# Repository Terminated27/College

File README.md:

# College
This is everything I have done in college so far.

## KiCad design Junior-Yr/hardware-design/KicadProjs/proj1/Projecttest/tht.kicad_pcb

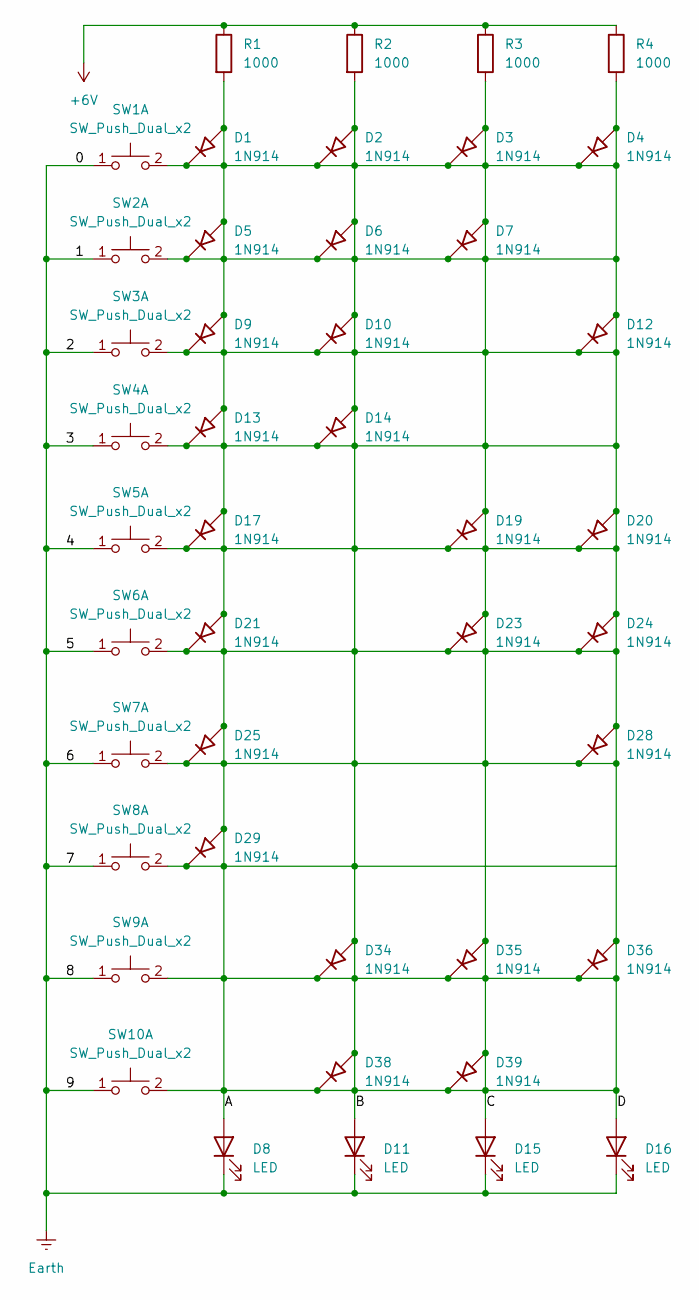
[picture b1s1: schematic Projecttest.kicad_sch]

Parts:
D1, D2, D3, D4, D5, D6, D7, D9, D10, D12, D13, D14, D17, D19, D20, D21, D23, D24, D25, D28, D29, D34, D35, D36, D38, D39: 1N914; AFL-W2C8.9D
D8, D11, D15, D16: LED; LED_D1.8mm_W1.8mm_H2.4mm_Horizontal_O1.27mm_Z1.6mm
R1, R2, R3, R4: 1000; R_Axial_DIN0204_L3.6mm_D1.6mm_P2.54mm_Vertical
SW1, SW2, SW3, SW4, SW5, SW6, SW7, SW8, SW9, SW10: SW_Push_Dual_x2; SW_Cherry_MX_1.00u_PCB

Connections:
+6V: R1.1, R2.1, R3.1, R4.1
/A: D1.1 (K), D1.2 (A), D2.1 (K), D2.2 (A), D3.1 (K), D3.2 (A), D4.1 (K), D4.2 (A), D5.1 (K), D5.2 (A), D6.1 (K), D6.2 (A), D7.1 (K), D7.2 (A), D8.2 (A), D9.1 (K), D9.2 (A), D10.1 (K), D10.2 (A), D11.2 (A), D12.1 (K), D12.2 (A), D13.1 (K), D13.2 (A), D14.1 (K), D14.2 (A), D15.2 (A), D16.2 (A), D17.1 (K), D17.2 (A), D19.1 (K), D19.2 (A), D20.1 (K), D20.2 (A), D21.1 (K), D21.2 (A), D23.1 (K), D23.2 (A), D24.1 (K), D24.2 (A), D25.1 (K), D25.2 (A), D28.1 (K), D28.2 (A), D29.1 (K), D29.2 (A), D34.1 (K), D34.2 (A), D35.1 (K), D35.2 (A), D36.1 (K), D36.2 (A), D38.1 (K), D38.2 (A), D39.1 (K), D39.2 (A), R1.2, R2.2, R3.2, R4.2, SW1.2 (D), SW2.2 (D), SW3.2 (D), SW4.2 (D), SW5.2 (D), SW6.2 (D), SW7.2 (D), SW8.2 (D), SW9.2 (D), SW10.2 (D)
Earth: D8.1 (K), D11.1 (K), D15.1 (K), D16.1 (K), SW1.1 (C), SW2.1 (C), SW3.1 (C), SW4.1 (C), SW5.1 (C), SW6.1 (C), SW7.1 (C), SW8.1 (C), SW9.1 (C), SW10.1 (C)

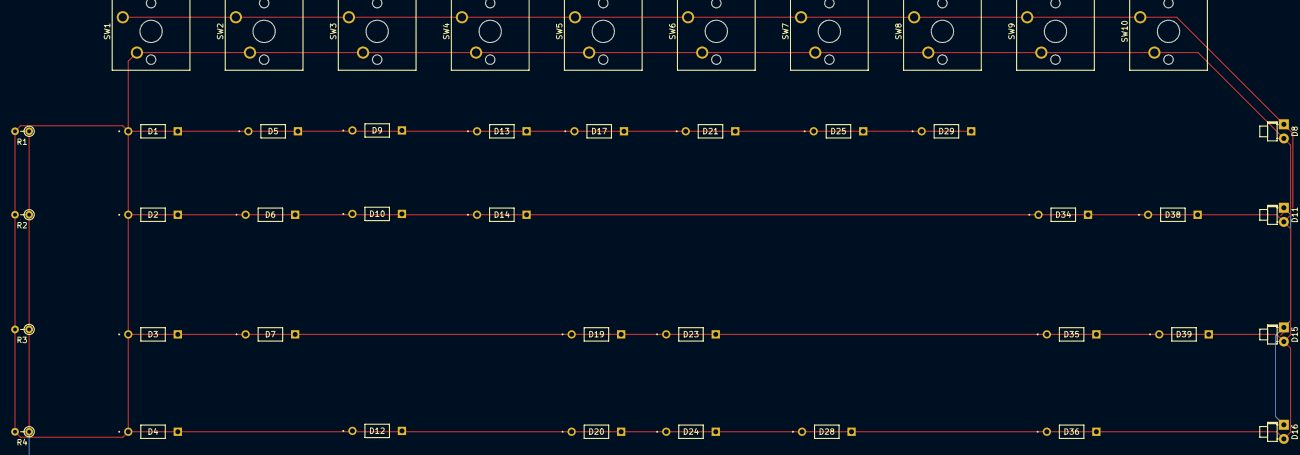
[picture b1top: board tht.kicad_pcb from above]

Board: 2 copper layers, 44 parts (0 on the bottom side), 3 nets.

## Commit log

2024-10-21 10-21-24 freshman year eosX13
2024-10-21 10-21-24 sophomore year eosX13
2024-10-21 everything else 10-21-24 eosX13
2024-10-21 10-21-24 eosX13
2024-10-24 10-24-2024 eosX13
2024-10-28 10-28-24 eoxX13
2024-10-29 10-29-2024 eosX13
2024-10-29 322 in_cmd
2024-10-29 builtin_cmd
2024-10-30 do_bgfg and waitfg
2024-10-31 10-31-2024 eosX13
2024-11-06 ece331 proj
2024-11-07 fixed up everything in project
2024-11-08 added course selection forms
2024-11-13 11/13/24 eosX13
2024-12-07 project2
2024-12-09 Project2 331
